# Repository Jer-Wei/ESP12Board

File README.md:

# ESP12Board
KiCad PCB design for ESP12 projects board.
This becomes my personal 'universal' breakout board for the ESP12.

- As small as possible
- Solderable by beginners
- Cheap components
- Feature rich

Get the latest release from: https://github.com/Thijxx/ESP12Board/releases

*I sent v2 to the manufacturer*

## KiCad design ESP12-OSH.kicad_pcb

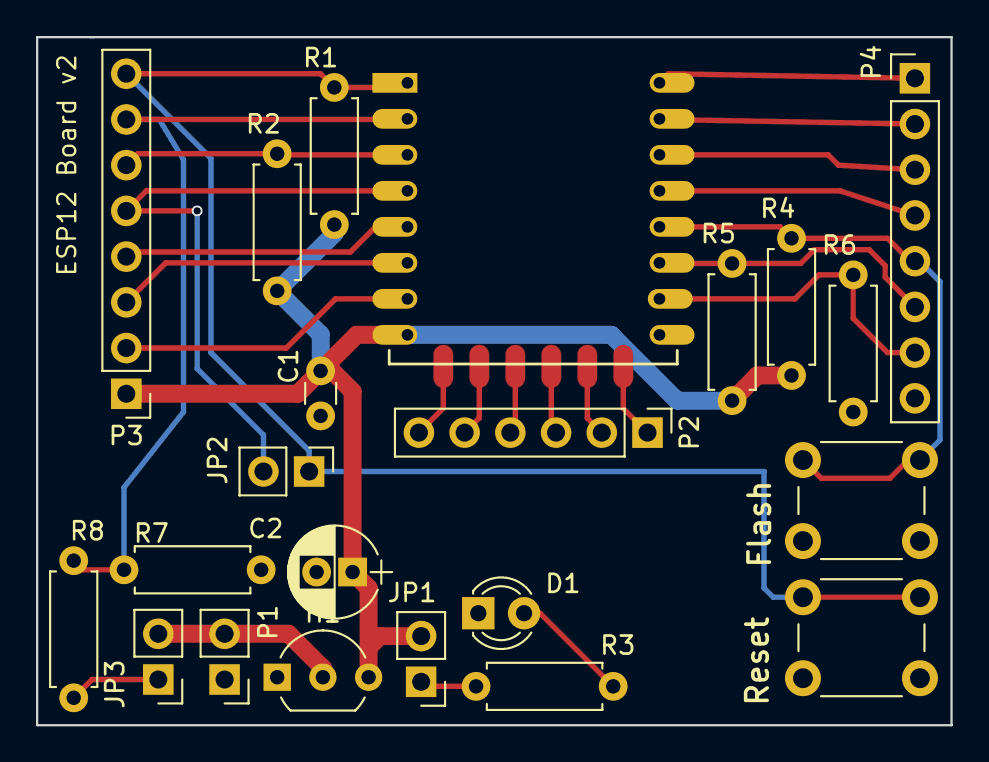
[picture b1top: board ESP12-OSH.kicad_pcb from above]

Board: 2 copper layers, 50.8 x 38.2 mm, 23 parts (1 on the bottom side), 26 nets.

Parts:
C1: 100nF; C_Disc_D3.0mm_W1.6mm_P2.50mm
C2: 0.1uF; CP_Radial_D5.0mm_P2.00mm
D1: LED; LED_D3.0mm
H1: HT7333; TO-92_Inline_Wide
JP1, JP2, JP3: Jumper; Pin_Header_Straight_1x02_Pitch2.54mm
LOGO: newlogo
P1: CONN_01X02; Pin_Header_Straight_1x02_Pitch2.54mm
P2: CONN_01X06; Pin_Header_Straight_1x06_Pitch2.54mm
P3, P4: CONN_01X08; Pin_Header_Straight_1x08_Pitch2.54mm
R1, R2, R4, R5, R6: 10K; R_Axial_DIN0207_L6.3mm_D2.5mm_P7.62mm_Horizontal
R3: 1K; R_Axial_DIN0207_L6.3mm_D2.5mm_P7.62mm_Horizontal
R7: 100K; R_Axial_DIN0207_L6.3mm_D2.5mm_P7.62mm_Horizontal
R8: 470K; R_Axial_DIN0207_L6.3mm_D2.5mm_P7.62mm_Horizontal
SW1, SW2: SW_Push; SW_PUSH_6mm
U1: ESP-12E

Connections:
/ADC: P3.7, R7.1, R8.2, U1.2
/CH_PD: P3.6, R2.1, U1.3
/CSO: P2.6, U1.17
/GPIO0: P4.5, R4.2, SW2.1, U1.12
/GPIO2: P4.6, R5.2, U1.11
/GPIO4: P4.4, U1.13
/GPIO5: P4.3, U1.14
/GPIO09: P2.4, U1.19
/GPIO10: P2.3, U1.20
/GPIO12: P3.3, U1.6
/GPIO13: P3.2, U1.7
/GPIO14: P3.4, U1.5
/GPIO15: P4.7, R6.2, U1.10
/GPIO16: JP2.2, P3.5, U1.4
/MISO: P2.5, U1.18
/MOSI: P2.2, U1.21
/REST: JP2.1, P3.8, R1.1, SW1.1, U1.1
/RX: P4.2, U1.15
/SCLK: P2.1, U1.22
/TX: P4.1, U1.16
/VCC: C1.1, C2.1, H1.3, JP1.2, P3.1, R1.2, R2.2, R4.1, R5.1, U1.8
/VIN: H1.2, JP3.2, P1.2
GND: C1.2, C2.2, D1.1, H1.1, P1.1, P4.8, R6.1, R7.2, SW1.2, SW2.2, U1.9
unnamed: D1.2, R3.2
unnamed: JP1.1, R3.1
unnamed: JP3.1, R8.1

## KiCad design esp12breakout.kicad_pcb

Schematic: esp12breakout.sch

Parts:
C1: 0.1uF; CP_Radial_D5.0mm_P2.00mm
D1: LED; LED_D3.0mm
J1: Screw_Terminal_1x02; TerminalBlock_Pheonix_MKDS1.5-2pol
JP1, JP2: Jumper; Pin_Header_Straight_1x02_Pitch2.00mm
P1, P2: CONN_01X08; Pin_Header_Straight_1x08_Pitch2.00mm
P3: CONN_01X06; Pin_Header_Straight_1x06_Pitch2.00mm
R2: 100; R_Axial_DIN0207_L6.3mm_D2.5mm_P7.62mm_Horizontal
R3: 1K; R_Axial_DIN0207_L6.3mm_D2.5mm_P7.62mm_Horizontal
R4: 10K; R_Axial_DIN0207_L6.3mm_D2.5mm_P7.62mm_Horizontal
U1: SPX2920U-3.3; TO-220
U2: ESP-12E

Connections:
ADC: P2.7, U2.2 (ADC)
CH_PD: P2.6, R2.2
CSO: P3.6, U2.17 (CS0)
GND: C1.2, D1.1 (K), J1.2, P1.8, R4.1, U1.2, U2.9 (GND)
GPIO0: P1.5, U2.12 (GPIO0)
GPIO2: P1.6, U2.11 (GPIO2)
GPIO4: P1.4, U2.13 (GPIO4)
GPIO5: P1.3, U2.14 (GPIO5)
GPIO9: P3.4, U2.19 (GPIO9)
GPIO10: P3.3, U2.20 (GPIO10)
GPIO12: P2.3, U2.6 (GPIO12)
GPIO13: P2.2, U2.7 (GPIO13)
GPIO14: P2.4, U2.5 (GPIO14)
GPIO15: P1.7, R4.2, U2.10 (GPIO15)
GPIO16: JP1.2, P2.5, U2.4 (GPIO16)
MISO: P3.5, U2.18 (MISO)
MOSI: P3.2, U2.21 (MOSI)
unnamed: D1.2 (A), R3.2
unnamed: J1.1, U1.1
unnamed: JP2.1, R3.1
unnamed: R2.1, U2.3 (CH_PD)
REST: JP1.1, P2.8, U2.1 (REST)
RX: P1.2, U2.15 (RXD)
SCLK: P3.1, U2.22 (SCLK)
TX: P1.1, U2.16 (TXD)
VCC: C1.1, JP2.2, P2.1, U1.3, U2.8 (VCC)

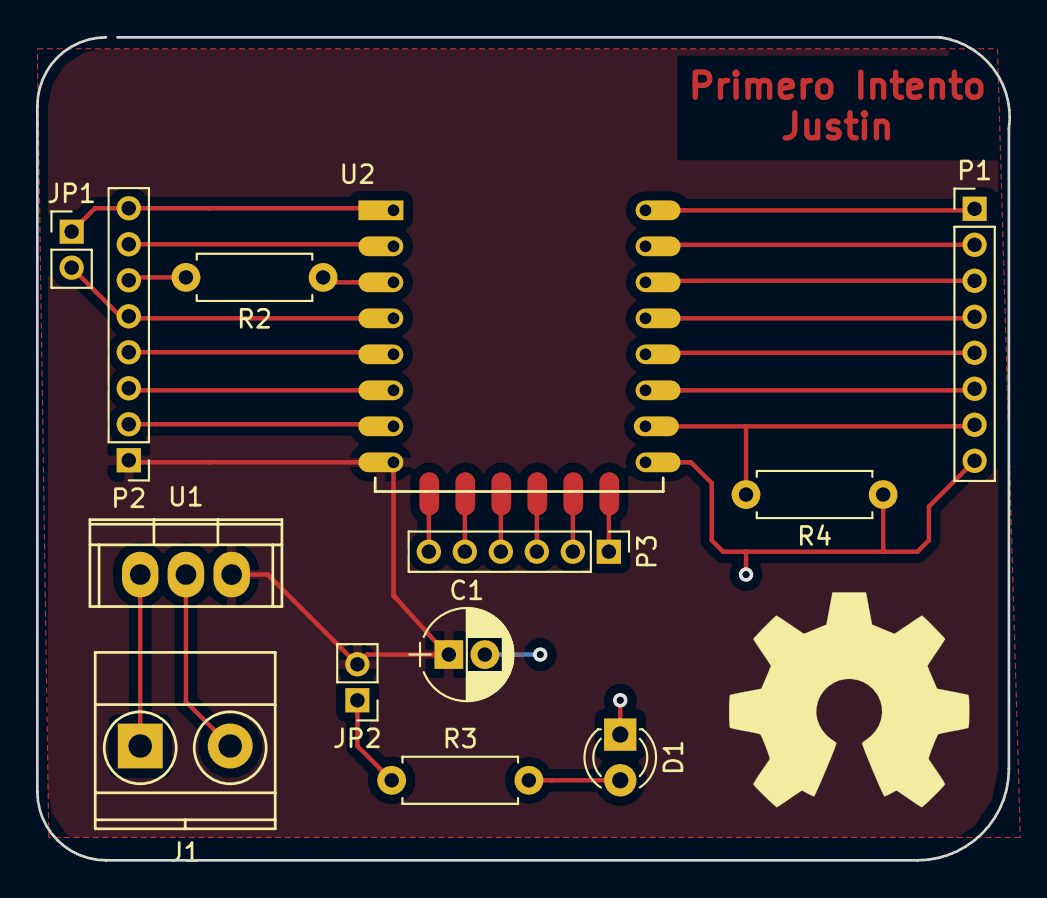
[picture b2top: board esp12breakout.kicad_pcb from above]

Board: 2 copper layers, 54.0 x 45.7 mm, 13 parts (0 on the bottom side), 26 nets.

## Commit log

2017-02-27 first version of ESP12 board
2017-02-27 power input en vias
2017-03-04 reworked, based on OSH Park template for KiCad
2017-03-04 cleanup
2017-03-04 backup
2017-03-04 headers with 2.54mm spacing
2017-03-05 commit before SO question
2017-03-05 extra small cap, moved large cap, removed front zone VCC, removed vias, moved parts around, added mounting holes
2017-03-16 images of v1 added
2017-03-16 added information and pictures
2017-03-16 small fix on readme
2017-03-22 done and dusted v1
2017-03-23 Update README.md
    updated wishlist, got the brainwave that these wishes should be tickets :D
2017-03-23 Update README.md
    less in readme, tickets created for bugs and whislist
2017-03-25 Update README.md
    added power consumption measurements
2017-03-28 switches for control and start with voltage divider for battery capacity management
2017-03-28 setup for version 2
2017-03-28 footprint fix for HT7333
2017-03-29 version 2 in the works!
2017-03-29 v2 work in progress images
2017-03-29 Update README.md
    added v2 work in progress pictures
2017-04-02 thicker traces, antenna outside of pcb, shorter traces, removed custom HT7333 footprint
2017-04-04 text on back and front silk improved
2017-04-12 mini tweaks before sending the design to the manufacturer
2017-04-12 new images for readme
